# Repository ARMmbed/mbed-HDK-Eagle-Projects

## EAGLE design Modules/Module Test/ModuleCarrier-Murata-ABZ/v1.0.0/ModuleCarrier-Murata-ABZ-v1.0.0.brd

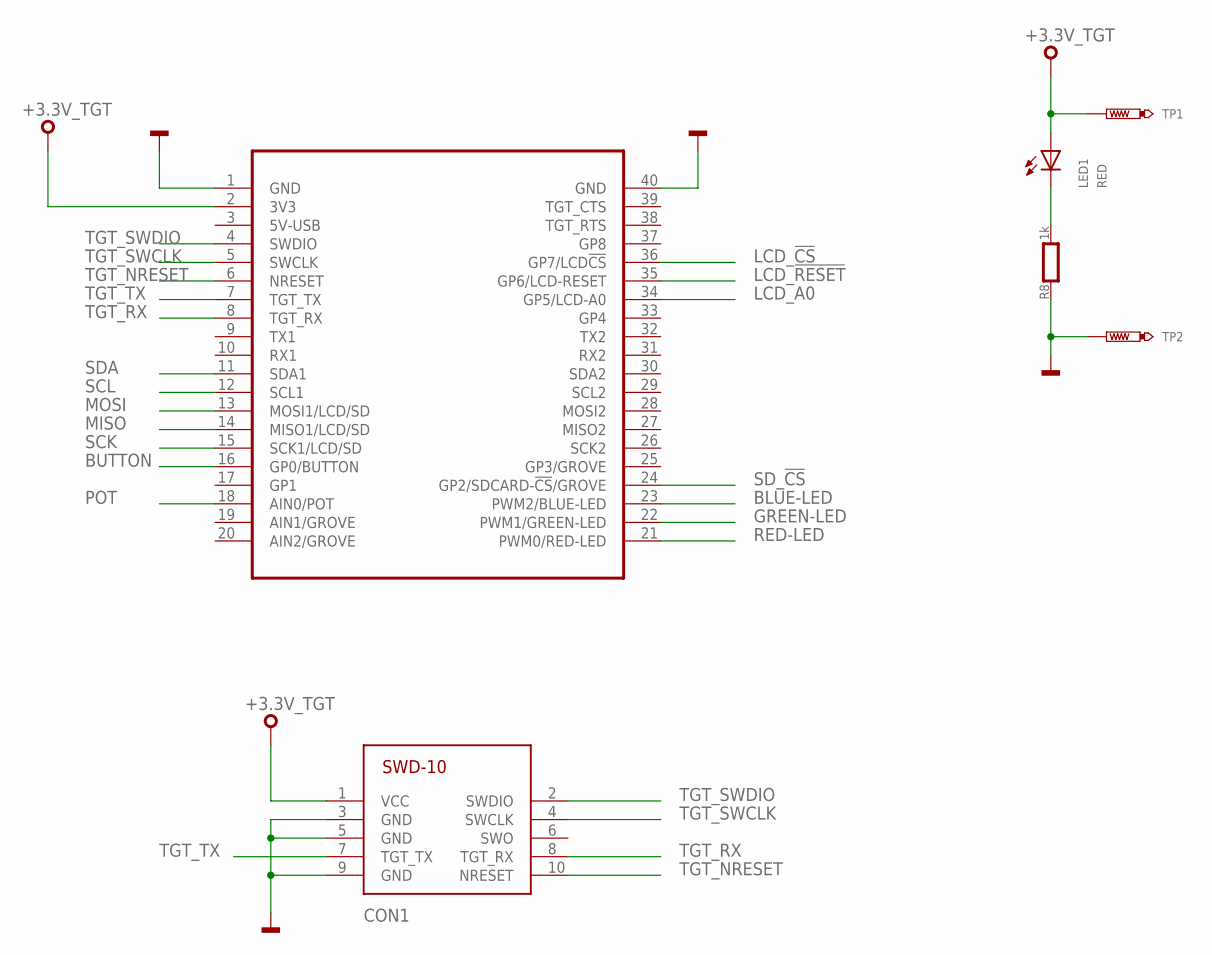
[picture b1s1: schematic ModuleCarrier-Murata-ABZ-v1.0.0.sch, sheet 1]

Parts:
CON1: SWD-10/TC2050_SMD; FTSH-105-02
LED1: RED; CHIPLED_0603
MOD1: MODULE_DAUGHTER
R8: 1k; 0603
TP1, TP2: TEST-POINT-50R-PTH; TP50-PTH

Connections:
+3.3V_TGT: CON1.1 (VCC), LED1.A, MOD1.2 (3V3), TP1.TP; also elsewhere on the board
BLUE-LED: MOD1.23 (PWM2/BLUE-LED); also elsewhere on the board
BUTTON: MOD1.16 (GP0/BUTTON); also elsewhere on the board
GND: CON1.3 (GND), CON1.5 (GND), CON1.9 (GND), MOD1.1 (GND), MOD1.40 (GND), R8.1, TP2.TP; also elsewhere on the board
GREEN-LED: MOD1.22 (PWM1/GREEN-LED); also elsewhere on the board
LCD_!CS: MOD1.36 (GP7/LCD!CS); also elsewhere on the board
LCD_!RESET: MOD1.35 (GP6/LCD-RESET); also elsewhere on the board
LCD_A0: MOD1.34 (GP5/LCD-A0); also elsewhere on the board
MISO: MOD1.14 (MISO1/LCD/SD); also elsewhere on the board
MOSI: MOD1.13 (MOSI1/LCD/SD); also elsewhere on the board
PA_1: LED1.C, R8.2
POT: MOD1.18 (AIN0/POT); also elsewhere on the board
RED-LED: MOD1.21 (PWM0/RED-LED); also elsewhere on the board
SCK: MOD1.15 (SCK1/LCD/SD); also elsewhere on the board
SCL: MOD1.12 (SCL1); also elsewhere on the board
SDA: MOD1.11 (SDA1); also elsewhere on the board
SD_!CS: MOD1.24 (GP2/SDCARD-!CS!/GROVE); also elsewhere on the board
TGT_NRESET: CON1.10 (NRESET), MOD1.6 (NRESET); also elsewhere on the board
TGT_RX: CON1.8 (TGT_RX), MOD1.8 (TGT_RX); also elsewhere on the board
TGT_SWCLK: CON1.4 (SWCLK), MOD1.5 (SWCLK); also elsewhere on the board
TGT_SWDIO: CON1.2 (SWDIO), MOD1.4 (SWDIO); also elsewhere on the board
TGT_TX: CON1.7 (TGT_TX), MOD1.7 (TGT_TX); also elsewhere on the board

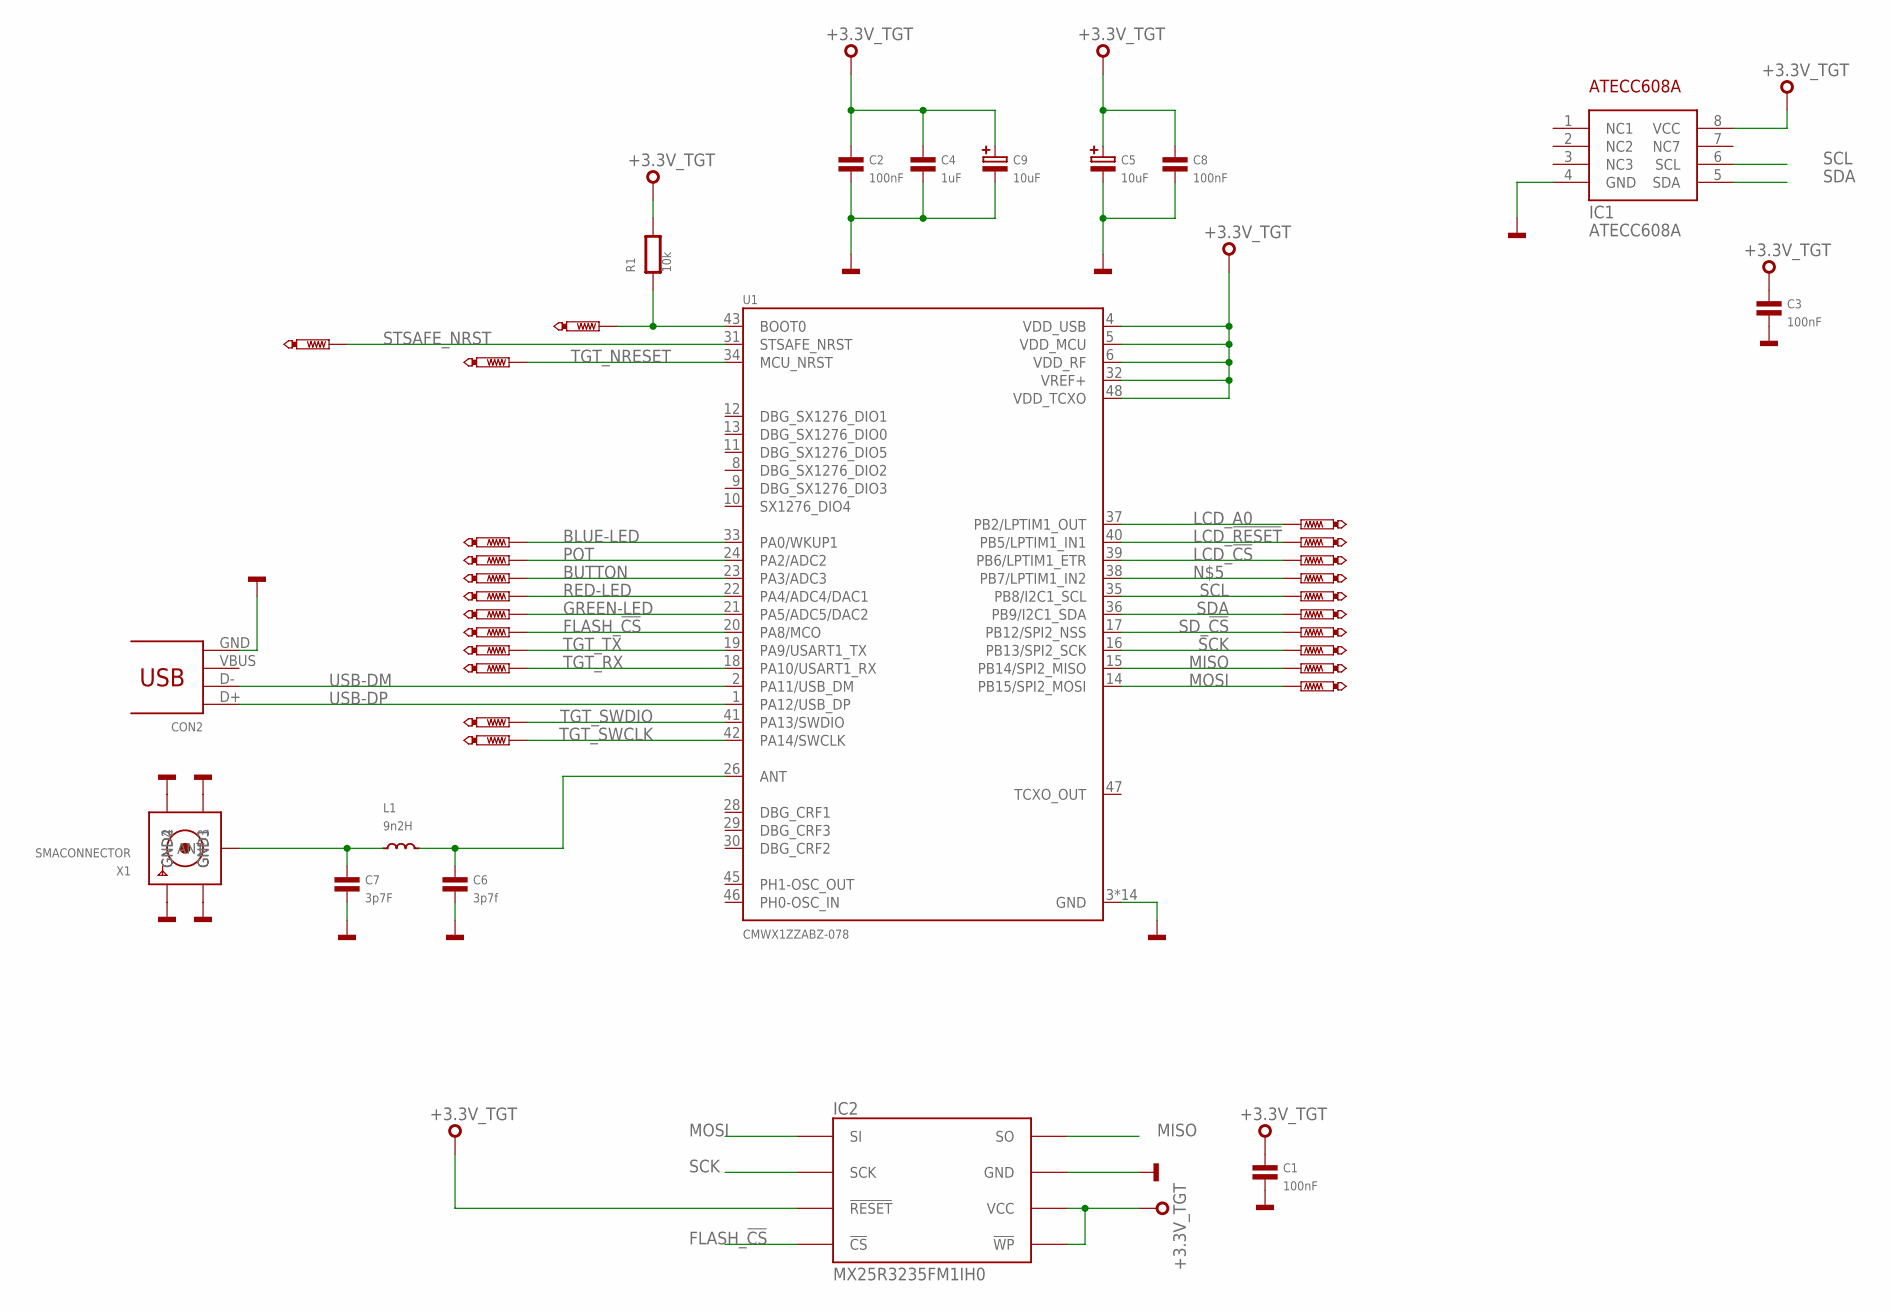
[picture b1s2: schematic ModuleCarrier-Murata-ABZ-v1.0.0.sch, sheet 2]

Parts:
C1, C2, C3, C8: 100nF; 0603
C4: 1uF; 0603
C5, C9: 10uF; SMC_B
C6: 3p7f; 0603
C7: 3p7F; 0603
CON2: 10033526-N3212MLF; USB-MINI-B-H
IC1: ATECC608A; SO8
IC2: MX25R3235FM1IH0; SO8
L1: 9n2H; 0603
R1: 10k; 0603
TP3, TP4, TP5, TP6, TP7, TP8, TP9, TP10, TP11, TP12, TP13, TP14, TP15, TP21, TP22, TP23, TP24, TP25, TP26, TP27, TP28, TP29, TP30: PTR1TP08R; TP08R
U1: CMWX1ZZABZ-078; XCVR_CMWX1ZZABZ-078
X1: SMACONNECTOR; SMA90_DIP

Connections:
+3.3V_TGT: C1.1, C2.1, C3.1, C4.1, C5.+, C8.1, C9.+, IC1.8 (VCC), IC2.3 (!WP), IC2.7 (!RESET), IC2.8 (VCC), R1.2, U1.4 (VDD_USB), U1.5 (VDD_MCU), U1.6 (VDD_RF), U1.32 (VREF+), U1.48 (VDD_TCXO); also elsewhere on the board
BLUE-LED: TP30.TP, U1.33 (PA0/WKUP1); also elsewhere on the board
BUTTON: TP11.TP, U1.23 (PA3/ADC3); also elsewhere on the board
FLASH_!CS: IC2.1 (!CS), TP29.TP, U1.20 (PA8/MCO)
GND: C1.2, C2.2, C3.2, C4.2, C5.-, C6.2, C7.2, C8.2, C9.-, CON2.GND, IC1.4 (GND), IC2.4 (GND), U1.3 (GND), U1.7 (GND), U1.25 (GND), U1.27 (GND), U1.44 (GND), U1.49 (GND), U1.50 (GND), U1.51 (GND), U1.52 (GND), U1.53 (GND), U1.54 (GND), U1.55 (GND), U1.56 (GND), U1.57 (GND), X1.GND1, X1.GND2, X1.GND3, X1.GND4; also elsewhere on the board
GREEN-LED: TP28.TP, U1.21 (PA5/ADC5/DAC2); also elsewhere on the board
LCD_!CS: TP25.TP, U1.39 (PB6/LPTIM1_ETR); also elsewhere on the board
LCD_!RESET: TP7.TP, U1.40 (PB5/LPTIM1_IN1); also elsewhere on the board
LCD_A0: TP6.TP, U1.37 (PB2/LPTIM1_OUT); also elsewhere on the board
MISO: IC2.2 (SO), TP5.TP, U1.15 (PB14/SPI2_MISO); also elsewhere on the board
MOSI: IC2.5 (SI), TP4.TP, U1.14 (PB15/SPI2_MOSI); also elsewhere on the board
unnamed: R1.1, TP14.TP, U1.43 (BOOT0)
unnamed: TP26.TP, U1.38 (PB7/LPTIM1_IN2)
unnamed: C7.1, L1.1, X1.ANTENNA (ANT)
unnamed: C6.1, L1.2, U1.26 (ANT)
POT: TP10.TP, U1.24 (PA2/ADC2); also elsewhere on the board
RED-LED: TP24.TP, U1.22 (PA4/ADC4/DAC1); also elsewhere on the board
SCK: IC2.6 (SCK), TP3.TP, U1.16 (PB13/SPI2_SCK); also elsewhere on the board
SCL: IC1.6 (SCL), TP12.TP, U1.35 (PB8/I2C1_SCL); also elsewhere on the board
SDA: IC1.5 (SDA), TP13.TP, U1.36 (PB9/I2C1_SDA); also elsewhere on the board
SD_!CS: TP27.TP, U1.17 (PB12/SPI2_NSS); also elsewhere on the board
STSAFE_NRST: TP15.TP, U1.31 (STSAFE_NRST)
TGT_NRESET: TP21.TP, U1.34 (MCU_NRST); also elsewhere on the board
TGT_RX: TP9.TP, U1.18 (PA10/USART1_RX); also elsewhere on the board
TGT_SWCLK: TP22.TP, U1.42 (PA14/SWCLK); also elsewhere on the board
TGT_SWDIO: TP23.TP, U1.41 (PA13/SWDIO); also elsewhere on the board
TGT_TX: TP8.TP, U1.19 (PA9/USART1_TX); also elsewhere on the board
USB-DM: CON2.D-, U1.2 (PA11/USB_DM)
USB-DP: CON2.D+, U1.1 (PA12/USB_DP)

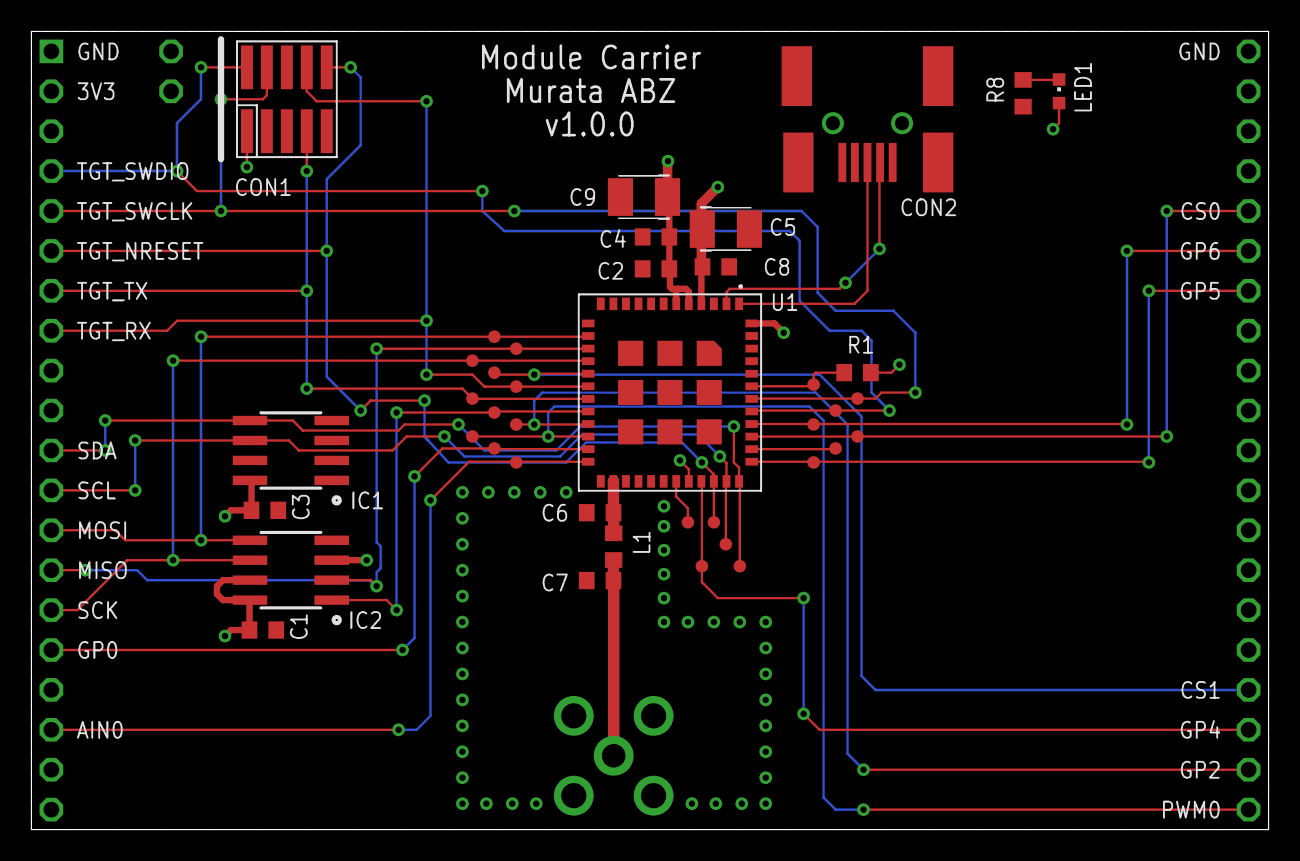
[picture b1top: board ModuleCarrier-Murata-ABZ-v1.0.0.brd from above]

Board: 2 copper layers, 78.7 x 50.8 mm, 45 parts (0 on the bottom side), 30 nets.

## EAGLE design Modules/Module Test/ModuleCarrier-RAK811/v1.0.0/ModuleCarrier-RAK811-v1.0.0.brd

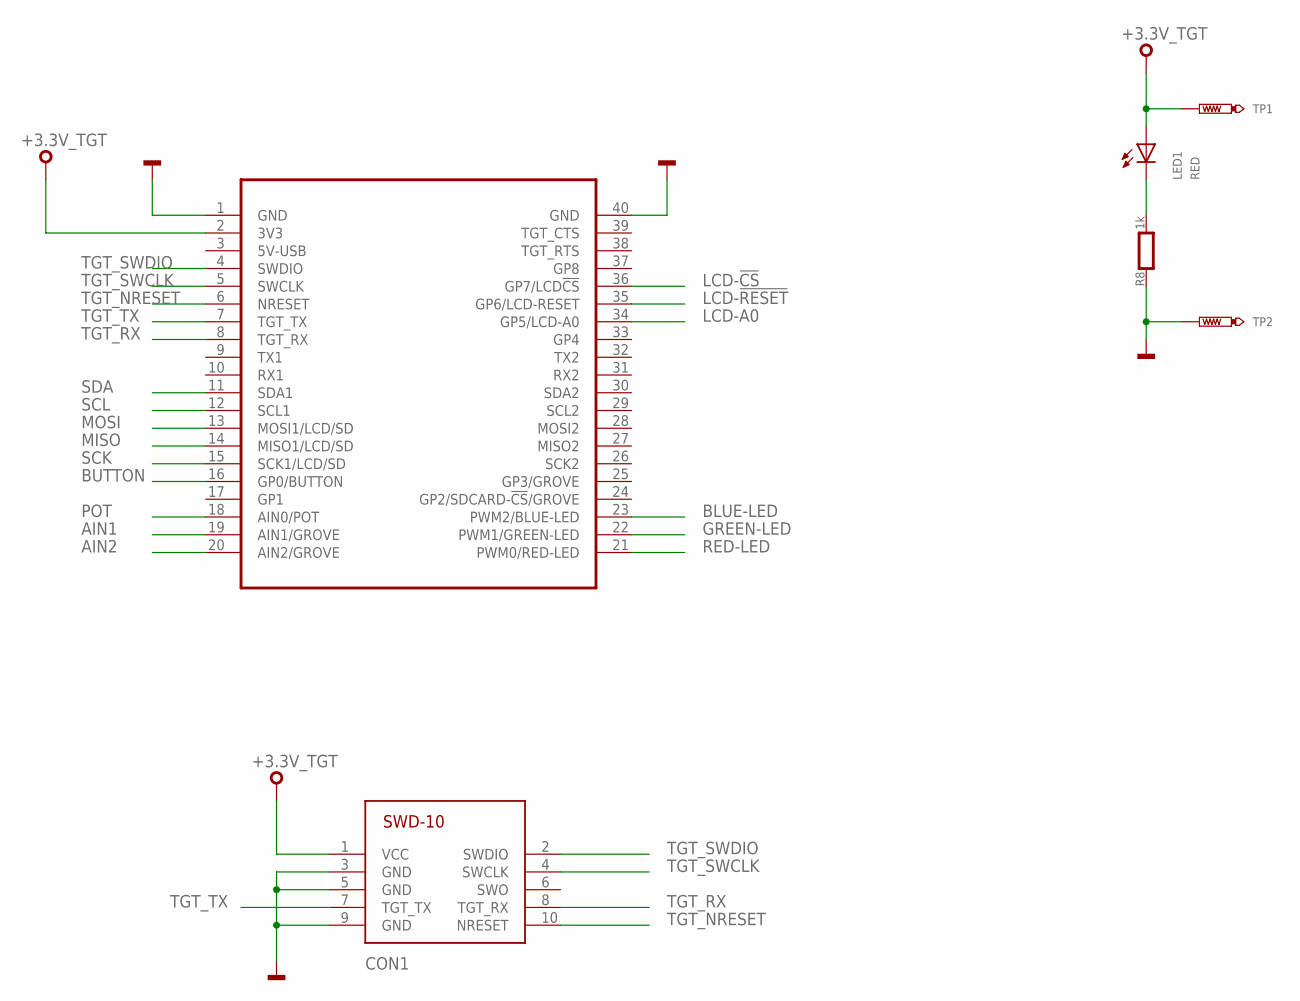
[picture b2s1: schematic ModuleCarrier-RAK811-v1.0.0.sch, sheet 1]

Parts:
CON1: SWD-10/TC2050_SMD; FTSH-105-02
LED1: RED; CHIPLED_0603
MOD2: MODULE_DAUGHTER
R8: 1k; 0603
TP1, TP2: TEST-POINT-50R-PTH; TP50-PTH

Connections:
+3.3V_TGT: CON1.1 (VCC), LED1.A, MOD2.2 (3V3), TP1.TP; also elsewhere on the board
AIN1: MOD2.19 (AIN1/GROVE); also elsewhere on the board
AIN2: MOD2.20 (AIN2/GROVE); also elsewhere on the board
BLUE-LED: MOD2.23 (PWM2/BLUE-LED); also elsewhere on the board
BUTTON: MOD2.16 (GP0/BUTTON); also elsewhere on the board
GND: CON1.3 (GND), CON1.5 (GND), CON1.9 (GND), MOD2.1 (GND), MOD2.40 (GND), R8.1, TP2.TP; also elsewhere on the board
GREEN-LED: MOD2.22 (PWM1/GREEN-LED); also elsewhere on the board
LCD-!CS: MOD2.36 (GP7/LCD!CS); also elsewhere on the board
LCD-!RESET: MOD2.35 (GP6/LCD-RESET); also elsewhere on the board
LCD-A0: MOD2.34 (GP5/LCD-A0); also elsewhere on the board
MISO: MOD2.14 (MISO1/LCD/SD); also elsewhere on the board
MOSI: MOD2.13 (MOSI1/LCD/SD); also elsewhere on the board
PA_1: LED1.C, R8.2
POT: MOD2.18 (AIN0/POT); also elsewhere on the board
RED-LED: MOD2.21 (PWM0/RED-LED); also elsewhere on the board
SCK: MOD2.15 (SCK1/LCD/SD); also elsewhere on the board
SCL: MOD2.12 (SCL1); also elsewhere on the board
SDA: MOD2.11 (SDA1); also elsewhere on the board
TGT_NRESET: CON1.10 (NRESET), MOD2.6 (NRESET); also elsewhere on the board
TGT_RX: CON1.8 (TGT_RX), MOD2.8 (TGT_RX); also elsewhere on the board
TGT_SWCLK: CON1.4 (SWCLK), MOD2.5 (SWCLK); also elsewhere on the board
TGT_SWDIO: CON1.2 (SWDIO), MOD2.4 (SWDIO); also elsewhere on the board
TGT_TX: CON1.7 (TGT_TX), MOD2.7 (TGT_TX); also elsewhere on the board

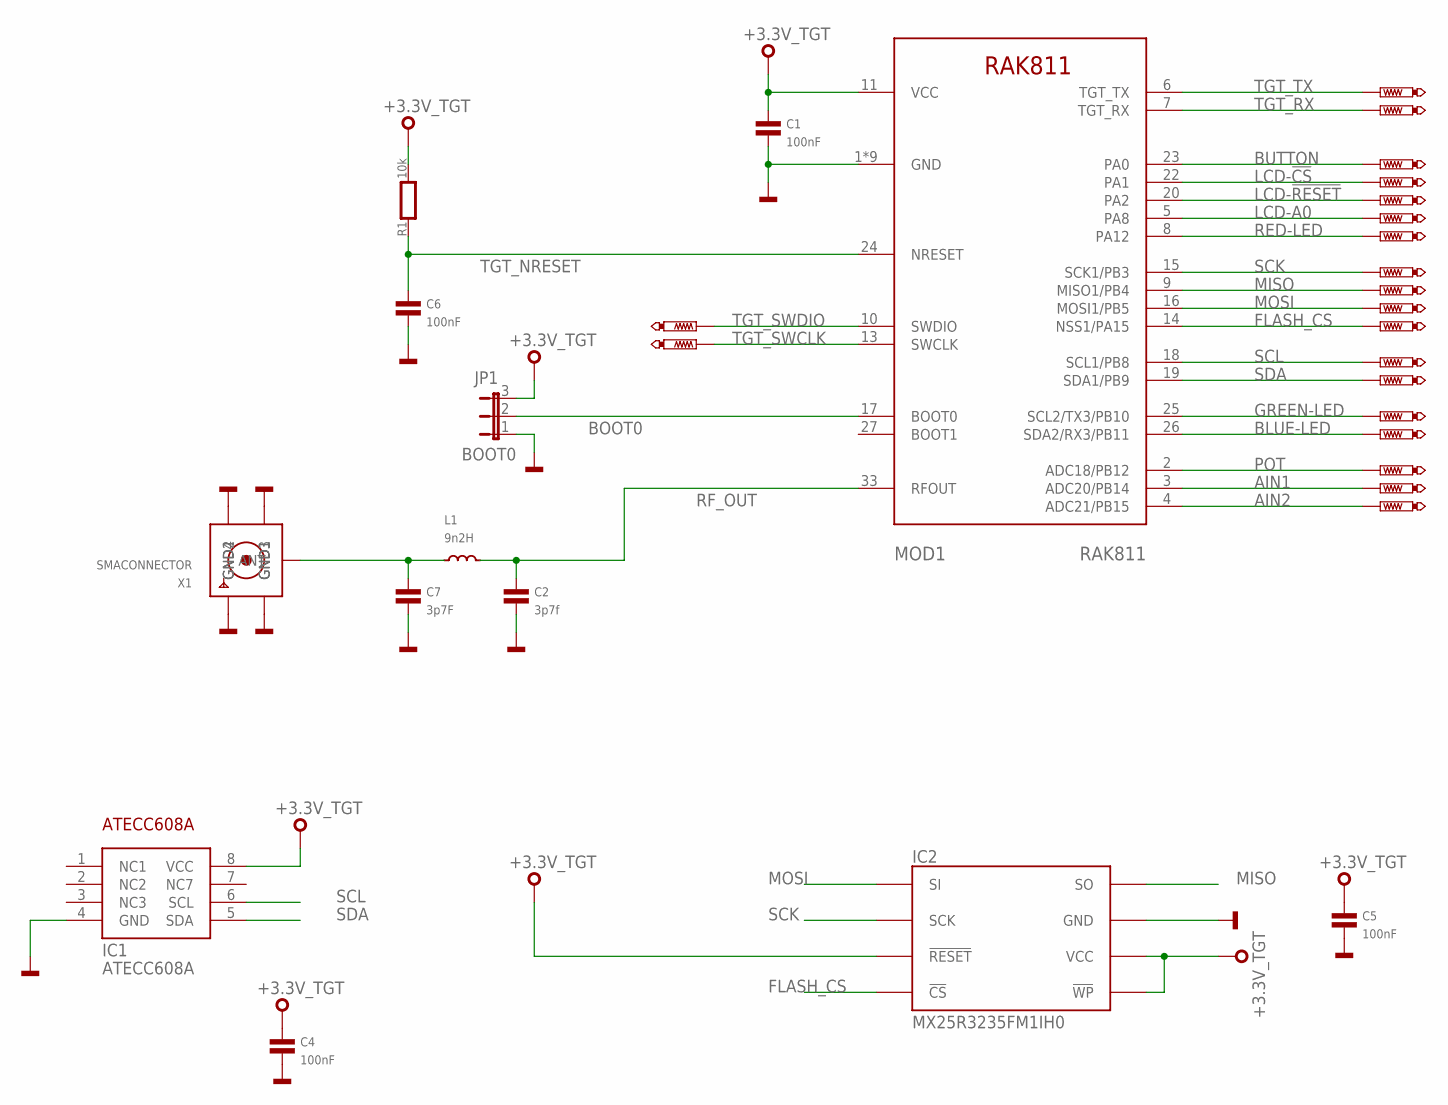
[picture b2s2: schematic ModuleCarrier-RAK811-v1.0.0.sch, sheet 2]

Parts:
C1, C4, C5, C6: 100nF; 0603
C2: 3p7f; 0603
C7: 3p7F; 0603
IC1: ATECC608A; SO8
IC2: MX25R3235FM1IH0; SO8
JP1: BOOT0; JP2
L1: 9n2H; 0603
MOD1: RAK811
R1: 10k; 0603
TP3, TP4, TP5, TP6, TP7, TP8, TP9, TP10, TP11, TP12, TP13, TP14, TP15, TP16, TP17, TP18, TP19, TP20, TP21, TP22: PTR1TP10R; TP10R
X1: SMACONNECTOR; SMA90_DIP

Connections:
+3.3V_TGT: C1.1, C4.1, C5.1, IC1.8 (VCC), IC2.3 (!WP), IC2.7 (!RESET), IC2.8 (VCC), JP1.3, MOD1.11 (VCC), R1.2; also elsewhere on the board
AIN1: MOD1.3 (ADC20/PB14), TP13.TP; also elsewhere on the board
AIN2: MOD1.4 (ADC21/PB15), TP12.TP; also elsewhere on the board
BLUE-LED: MOD1.26 (SDA2/RX3/PB11), TP15.TP; also elsewhere on the board
BOOT0: JP1.2, MOD1.17 (BOOT0)
BUTTON: MOD1.23 (PA0), TP7.TP; also elsewhere on the board
FLASH_CS: IC2.1 (!CS), MOD1.14 (NSS1/PA15), TP19.TP
GND: C1.2, C2.2, C4.2, C5.2, C6.2, C7.2, IC1.4 (GND), IC2.4 (GND), JP1.1, MOD1.1 (GND), MOD1.12 (GND), MOD1.21 (GND), MOD1.28 (GND), MOD1.29 (GND), MOD1.30 (GND), MOD1.31 (GND), MOD1.32 (GND), MOD1.34 (GND), X1.GND1, X1.GND2, X1.GND3, X1.GND4; also elsewhere on the board
GREEN-LED: MOD1.25 (SCL2/TX3/PB10), TP16.TP; also elsewhere on the board
LCD-!CS: MOD1.22 (PA1), TP8.TP; also elsewhere on the board
LCD-!RESET: MOD1.20 (PA2), TP9.TP; also elsewhere on the board
LCD-A0: MOD1.5 (PA8), TP10.TP; also elsewhere on the board
MISO: IC2.2 (SO), MOD1.9 (MISO1/PB4), TP21.TP; also elsewhere on the board
MOSI: IC2.5 (SI), MOD1.16 (MOSI1/PB5), TP20.TP; also elsewhere on the board
unnamed: C7.1, L1.1, X1.ANTENNA (ANT)
POT: MOD1.2 (ADC18/PB12), TP14.TP; also elsewhere on the board
RED-LED: MOD1.8 (PA12), TP11.TP; also elsewhere on the board
RF_OUT: C2.1, L1.2, MOD1.33 (RFOUT)
SCK: IC2.6 (SCK), MOD1.15 (SCK1/PB3), TP22.TP; also elsewhere on the board
SCL: IC1.6 (SCL), MOD1.18 (SCL1/PB8), TP18.TP; also elsewhere on the board
SDA: IC1.5 (SDA), MOD1.19 (SDA1/PB9), TP17.TP; also elsewhere on the board
TGT_NRESET: C6.1, MOD1.24 (NRESET), R1.1; also elsewhere on the board
TGT_RX: MOD1.7 (TGT_RX), TP6.TP; also elsewhere on the board
TGT_SWCLK: MOD1.13 (SWCLK), TP4.TP; also elsewhere on the board
TGT_SWDIO: MOD1.10 (SWDIO), TP3.TP; also elsewhere on the board
TGT_TX: MOD1.6 (TGT_TX), TP5.TP; also elsewhere on the board

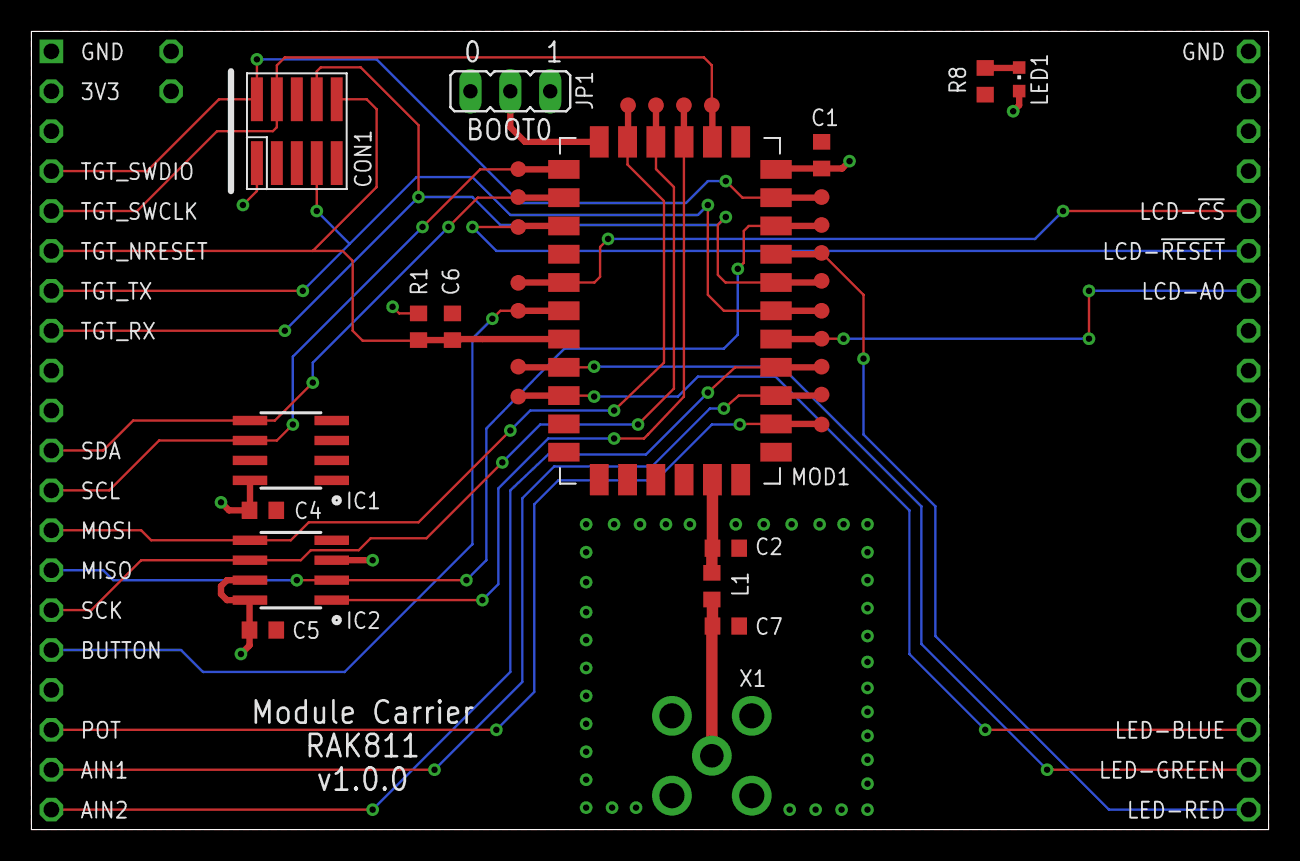
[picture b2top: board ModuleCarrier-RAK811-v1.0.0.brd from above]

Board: 2 copper layers, 78.7 x 50.8 mm, 39 parts (0 on the bottom side), 27 nets.

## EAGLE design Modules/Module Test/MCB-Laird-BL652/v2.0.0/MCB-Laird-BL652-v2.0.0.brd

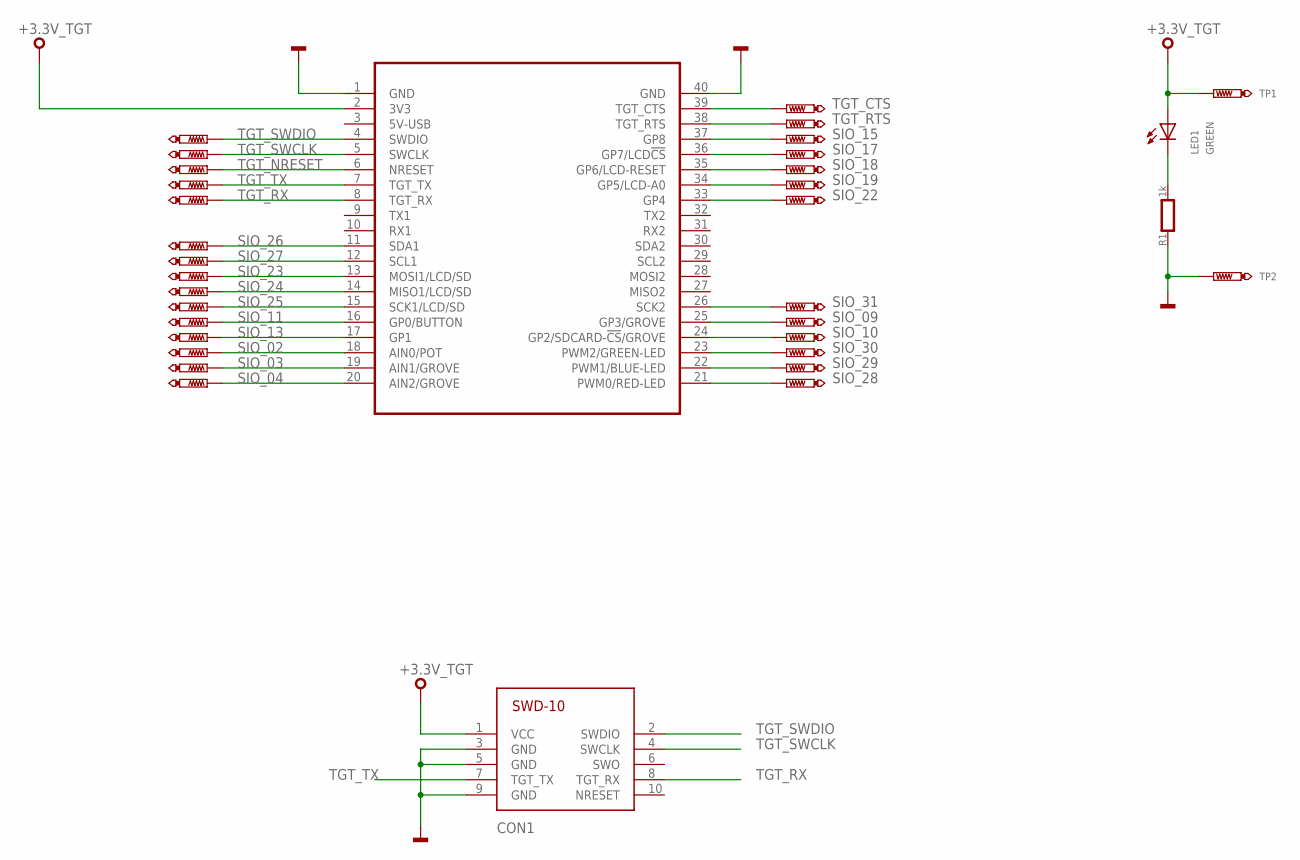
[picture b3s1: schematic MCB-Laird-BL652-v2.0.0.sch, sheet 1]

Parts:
CON1: SWD-10/TC2050_SMD; FTSH-105-02
LED1: GREEN; CHIPLED_0603
MOD1: MODULE_DAUGHTER
R1: 1k; 0603
TP1, TP2: TEST-POINT-50R-PTH; TP50-PTH
TP3, TP4, TP5, TP6, TP7, TP8, TP9, TP10, TP11, TP12, TP13, TP14, TP15, TP16, TP17, TP18, TP19, TP20, TP21, TP22, TP23, TP24, TP25, TP26, TP27, TP28, TP29, TP30: PTR1TP07R; TP07R

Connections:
+3.3V_TGT: CON1.1 (VCC), LED1.A, MOD1.2 (3V3), TP1.TP; also elsewhere on the board
GND: CON1.3 (GND), CON1.5 (GND), CON1.9 (GND), MOD1.1 (GND), MOD1.40 (GND), R1.1, TP2.TP; also elsewhere on the board
PA_1: LED1.C, R1.2
SIO_02: MOD1.18 (AIN0/POT), TP10.TP; also elsewhere on the board
SIO_03: MOD1.19 (AIN1/GROVE), TP11.TP; also elsewhere on the board
SIO_04: MOD1.20 (AIN2/GROVE), TP12.TP; also elsewhere on the board
SIO_09: MOD1.25 (GP3/GROVE), TP17.TP; also elsewhere on the board
SIO_10: MOD1.24 (GP2/SDCARD-!CS!/GROVE), TP16.TP; also elsewhere on the board
SIO_11: MOD1.16 (GP0/BUTTON), TP8.TP; also elsewhere on the board
SIO_13: MOD1.17 (GP1), TP9.TP; also elsewhere on the board
SIO_15: MOD1.37 (GP8), TP22.TP; also elsewhere on the board
SIO_17: MOD1.36 (GP7/LCD!CS), TP21.TP; also elsewhere on the board
SIO_18: MOD1.35 (GP6/LCD-RESET), TP20.TP; also elsewhere on the board
SIO_19: MOD1.34 (GP5/LCD-A0), TP19.TP; also elsewhere on the board
SIO_22: MOD1.33 (GP4), TP18.TP; also elsewhere on the board
SIO_23: MOD1.13 (MOSI1/LCD/SD), TP5.TP; also elsewhere on the board
SIO_24: MOD1.14 (MISO1/LCD/SD), TP6.TP; also elsewhere on the board
SIO_25: MOD1.15 (SCK1/LCD/SD), TP7.TP; also elsewhere on the board
SIO_26: MOD1.11 (SDA1), TP3.TP; also elsewhere on the board
SIO_27: MOD1.12 (SCL1), TP4.TP; also elsewhere on the board
SIO_28: MOD1.21 (PWM0/RED-LED), TP13.TP; also elsewhere on the board
SIO_29: MOD1.22 (PWM1/BLUE-LED), TP14.TP; also elsewhere on the board
SIO_30: MOD1.23 (PWM2/GREEN-LED), TP15.TP; also elsewhere on the board
SIO_31: MOD1.26 (SCK2), TP25.TP; also elsewhere on the board
TGT_CTS: MOD1.39 (TGT_CTS), TP24.TP; also elsewhere on the board
TGT_NRESET: MOD1.6 (NRESET), TP28.TP; also elsewhere on the board
TGT_RTS: MOD1.38 (TGT_RTS), TP23.TP; also elsewhere on the board
TGT_RX: CON1.8 (TGT_RX), MOD1.8 (TGT_RX), TP30.TP; also elsewhere on the board
TGT_SWCLK: CON1.4 (SWCLK), MOD1.5 (SWCLK), TP27.TP; also elsewhere on the board
TGT_SWDIO: CON1.2 (SWDIO), MOD1.4 (SWDIO), TP26.TP; also elsewhere on the board
TGT_TX: CON1.7 (TGT_TX), MOD1.7 (TGT_TX), TP29.TP; also elsewhere on the board

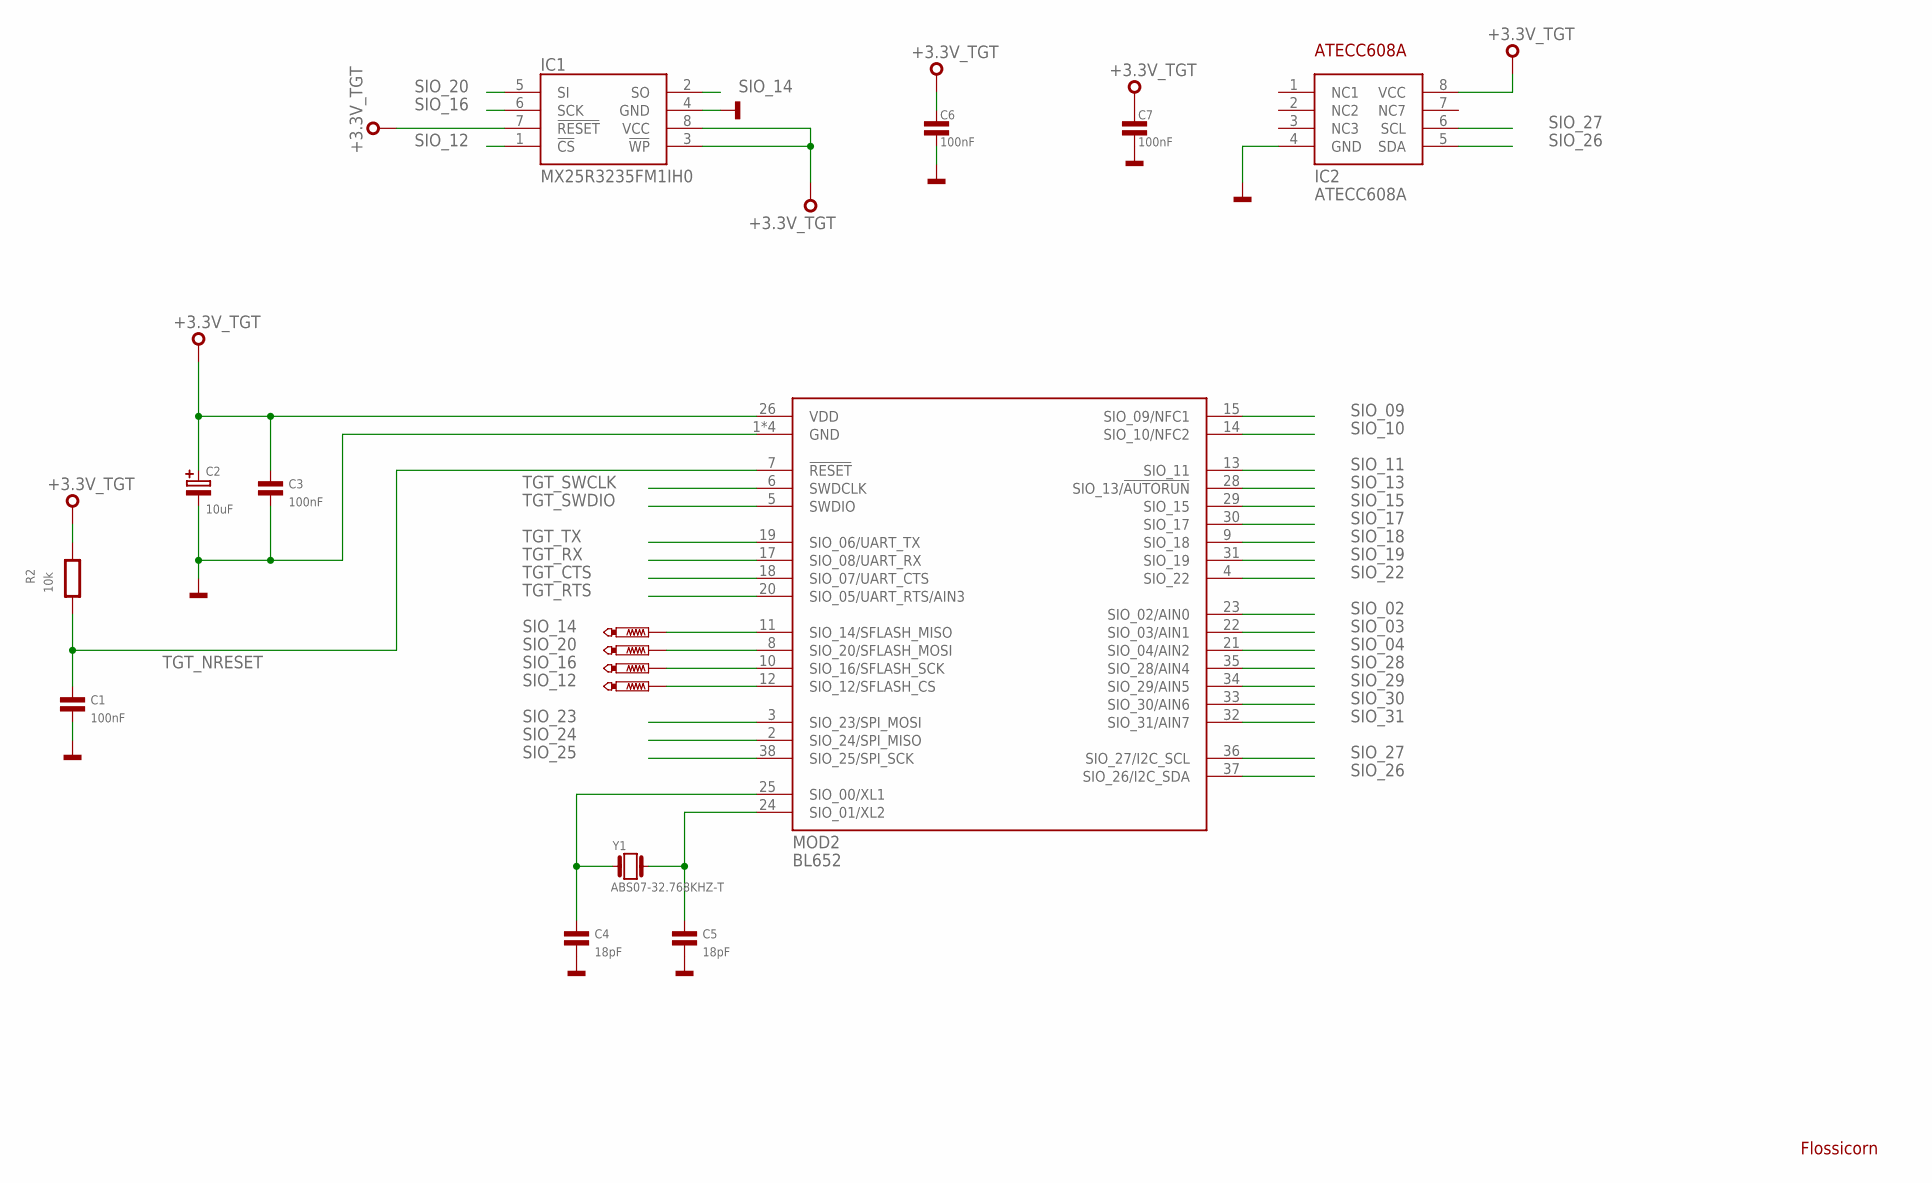
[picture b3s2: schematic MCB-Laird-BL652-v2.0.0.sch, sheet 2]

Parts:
C1, C3, C6, C7: 100nF; 0603
C2: 10uF; SMC_B
C4, C5: 18pF; 0603
IC1: MX25R3235FM1IH0; SO8
IC2: ATECC608A; SO8
MOD2: BL652
R2: 10k; 0603
SS1: FLOSSICORN0.25; FLOSSICORN-0.25
TP31, TP32, TP33, TP34: PTR1TP07R; TP07R
Y1: ABS07-32.768KHZ-T; FC135

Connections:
+3.3V_TGT: C2.+, C3.1, C6.1, C7.1, IC1.3 (!WP), IC1.7 (!RESET), IC1.8 (VCC), IC2.8 (VCC), MOD2.26 (VDD), R2.2; also elsewhere on the board
GND: C1.2, C2.-, C3.2, C4.2, C5.2, C6.2, C7.2, IC1.4 (GND), IC2.4 (GND), MOD2.1 (GND), MOD2.16 (GND), MOD2.27 (GND), MOD2.39 (GND); also elsewhere on the board
unnamed: C5.1, MOD2.24 (SIO_01/XL2), Y1.X2 (2)
unnamed: C4.1, MOD2.25 (SIO_00/XL1), Y1.X1 (1)
SIO_02: MOD2.23 (SIO_02/AIN0); also elsewhere on the board
SIO_03: MOD2.22 (SIO_03/AIN1); also elsewhere on the board
SIO_04: MOD2.21 (SIO_04/AIN2); also elsewhere on the board
SIO_09: MOD2.15 (SIO_09/NFC1); also elsewhere on the board
SIO_10: MOD2.14 (SIO_10/NFC2); also elsewhere on the board
SIO_11: MOD2.13 (SIO_11); also elsewhere on the board
SIO_12: IC1.1 (!CS), MOD2.12 (SIO_12/SFLASH_CS), TP34.TP
SIO_13: MOD2.28 (SIO_13/!AUTORUN); also elsewhere on the board
SIO_14: IC1.2 (SO), MOD2.11 (SIO_14/SFLASH_MISO), TP31.TP
SIO_15: MOD2.29 (SIO_15); also elsewhere on the board
SIO_16: IC1.6 (SCK), MOD2.10 (SIO_16/SFLASH_SCK), TP33.TP
SIO_17: MOD2.30 (SIO_17); also elsewhere on the board
SIO_18: MOD2.9 (SIO_18); also elsewhere on the board
SIO_19: MOD2.31 (SIO_19); also elsewhere on the board
SIO_20: IC1.5 (SI), MOD2.8 (SIO_20/SFLASH_MOSI), TP32.TP
SIO_22: MOD2.4 (SIO_22); also elsewhere on the board
SIO_23: MOD2.3 (SIO_23/SPI_MOSI); also elsewhere on the board
SIO_24: MOD2.2 (SIO_24/SPI_MISO); also elsewhere on the board
SIO_25: MOD2.38 (SIO_25/SPI_SCK); also elsewhere on the board
SIO_26: IC2.5 (SDA), MOD2.37 (SIO_26/I2C_SDA); also elsewhere on the board
SIO_27: IC2.6 (SCL), MOD2.36 (SIO_27/I2C_SCL); also elsewhere on the board
SIO_28: MOD2.35 (SIO_28/AIN4); also elsewhere on the board
SIO_29: MOD2.34 (SIO_29/AIN5); also elsewhere on the board
SIO_30: MOD2.33 (SIO_30/AIN6); also elsewhere on the board
SIO_31: MOD2.32 (SIO_31/AIN7); also elsewhere on the board
TGT_CTS: MOD2.18 (SIO_07/UART_CTS); also elsewhere on the board
TGT_NRESET: C1.1, MOD2.7 (!RESET), R2.1; also elsewhere on the board
TGT_RTS: MOD2.20 (SIO_05/UART_RTS/AIN3); also elsewhere on the board
TGT_RX: MOD2.17 (SIO_08/UART_RX); also elsewhere on the board
TGT_SWCLK: MOD2.6 (SWDCLK); also elsewhere on the board
TGT_SWDIO: MOD2.5 (SWDIO); also elsewhere on the board
TGT_TX: MOD2.19 (SIO_06/UART_TX); also elsewhere on the board

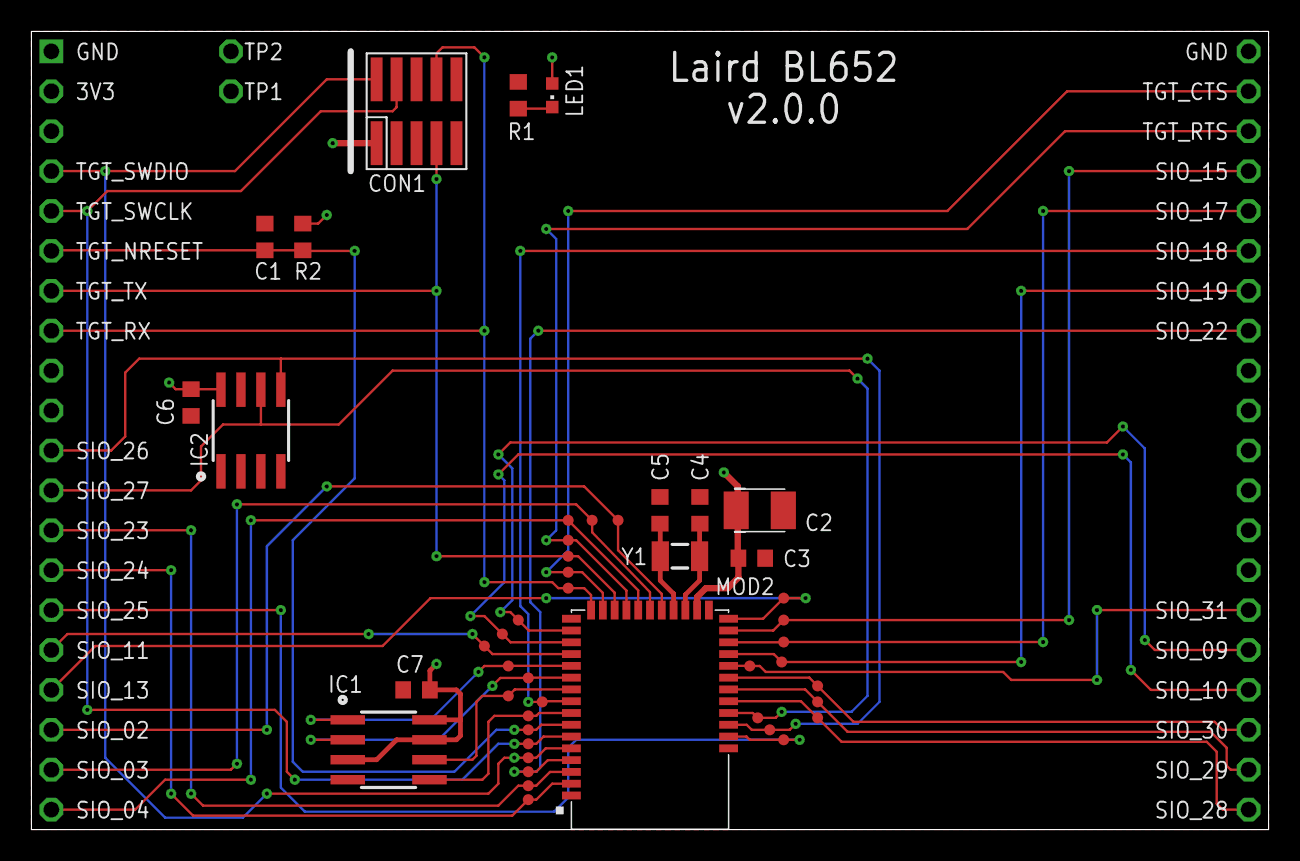
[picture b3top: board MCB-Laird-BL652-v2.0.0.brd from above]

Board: 2 copper layers, 78.7 x 50.8 mm, 51 parts (0 on the bottom side), 37 nets.

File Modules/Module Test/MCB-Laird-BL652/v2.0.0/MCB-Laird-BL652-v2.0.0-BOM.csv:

"Qty";"Value";"Device";"Package";"Parts";"Description";"MF";"MFN";"OC-DIGIKEY";"OC-MOUSER";"OC-NEWARK";"TP_SIGNAL_NAME";
"2";"100nF";"C0603";"0603";"C1, C3";"Capacitor";"";"";"";"";"";"";
"2";"100nF";"CAPACITOR0603";"0603";"C6, C7";"Capacitor";"";"";"";"";"";"";
"1";"10k";"RESISTOR0603";"0603";"R2";"Resistor";"";"";"";"";"";"";
"1";"10uF";"CAPACITOR-POLARISEDB";"SMC_B";"C2";"Polarised capacitor";"Kemet";"T491B106K020AT";"399-8298-1-ND";"80-T491B106K020";" 57K1740";"";
"2";"18pF";"C0603";"0603";"C4, C5";"Capacitor";"";"";"";"";"";"";
"1";"1k";"RESISTOR0603";"0603";"R1";"Resistor";"";"";"";"";"";"";
"1";"ABS07-32.768KHZ-T";"ABS07-32.768KHZ-T";"FC135";"Y1";"Crystal, Abracon 32.768kHz ±20ppm 12.5pF";"Abracon";"ABS07-32.768KHZ-T";"535-9542-1-ND";"535-9542-1-ND";"2101347";"";
"1";"ATECC608A";"ATECC608A";"SO8";"IC2";"I2C Secure element and crytpo accelerator";"Atmel";"ATECC608A";"ATECC608A-SSHCZ-TCT-ND ";"556-ATECC608ASSHDAB ";"";"";
"1";"BL652";"BL652";"BL652";"MOD2";"nRF52 Based BLE module";"Laird";"BL652";"";"239-BL652-SA-01";"2664536";"";
"1";"FLOSSICORN0.25";"FLOSSICORN0.25";"FLOSSICORN-0.25";"SS1";"";"";"";"";"";"";"";
"1";"GREEN";"SMD_LED0603";"CHIPLED_0603";"LED1";"LED SMD, Colour Red";"Wurth Electronics Inc";"150060RS75000";"732-4978-1-ND";"710-150060RS75000";"2322071";"";
"1";"MODULE_DAUGHTER";"MODULE_DAUGHTER";"MODULE_DAUGHTER";"MOD1";"";"";"";"";"";"";"";
"1";"MX25R3235FM1IH0";"MX25R3235FM1IH0";"SO8";"IC1";"Serial Flash 32 Mb 80 Mhz";"Macronix";"MX25R3235FM1IH0";"1092-1175-ND";"";"";"";
"32";"PTR1TP07R";"PTR1TP07R";"TP07R";"TP3, TP4, TP5, TP6, TP7, TP8, TP9, TP10, TP11, TP12, TP13, TP14, TP15, TP16, TP17, TP18, TP19, TP20, TP21, TP22, TP23, TP24, TP25, TP26, TP27, TP28, TP29, TP30, TP31, TP32, TP33, TP34";"TEST PIN";"";"";"";"";"";"";
"1";"SWD-10/TC2050_SMD";"SWD-10/TC2050_SMD";"FTSH-105-02";"CON1";"1mm pitch 10-Pin Cortex Programming Header with optional TC2050 footprint solderless interchangeable";"";"";"";"";"";"";
"2";"TEST-POINT-50R-PTH";"TEST-POINT-50R-PTH";"TP50-PTH";"TP1, TP2";"";"";"";"";"";"";"";
